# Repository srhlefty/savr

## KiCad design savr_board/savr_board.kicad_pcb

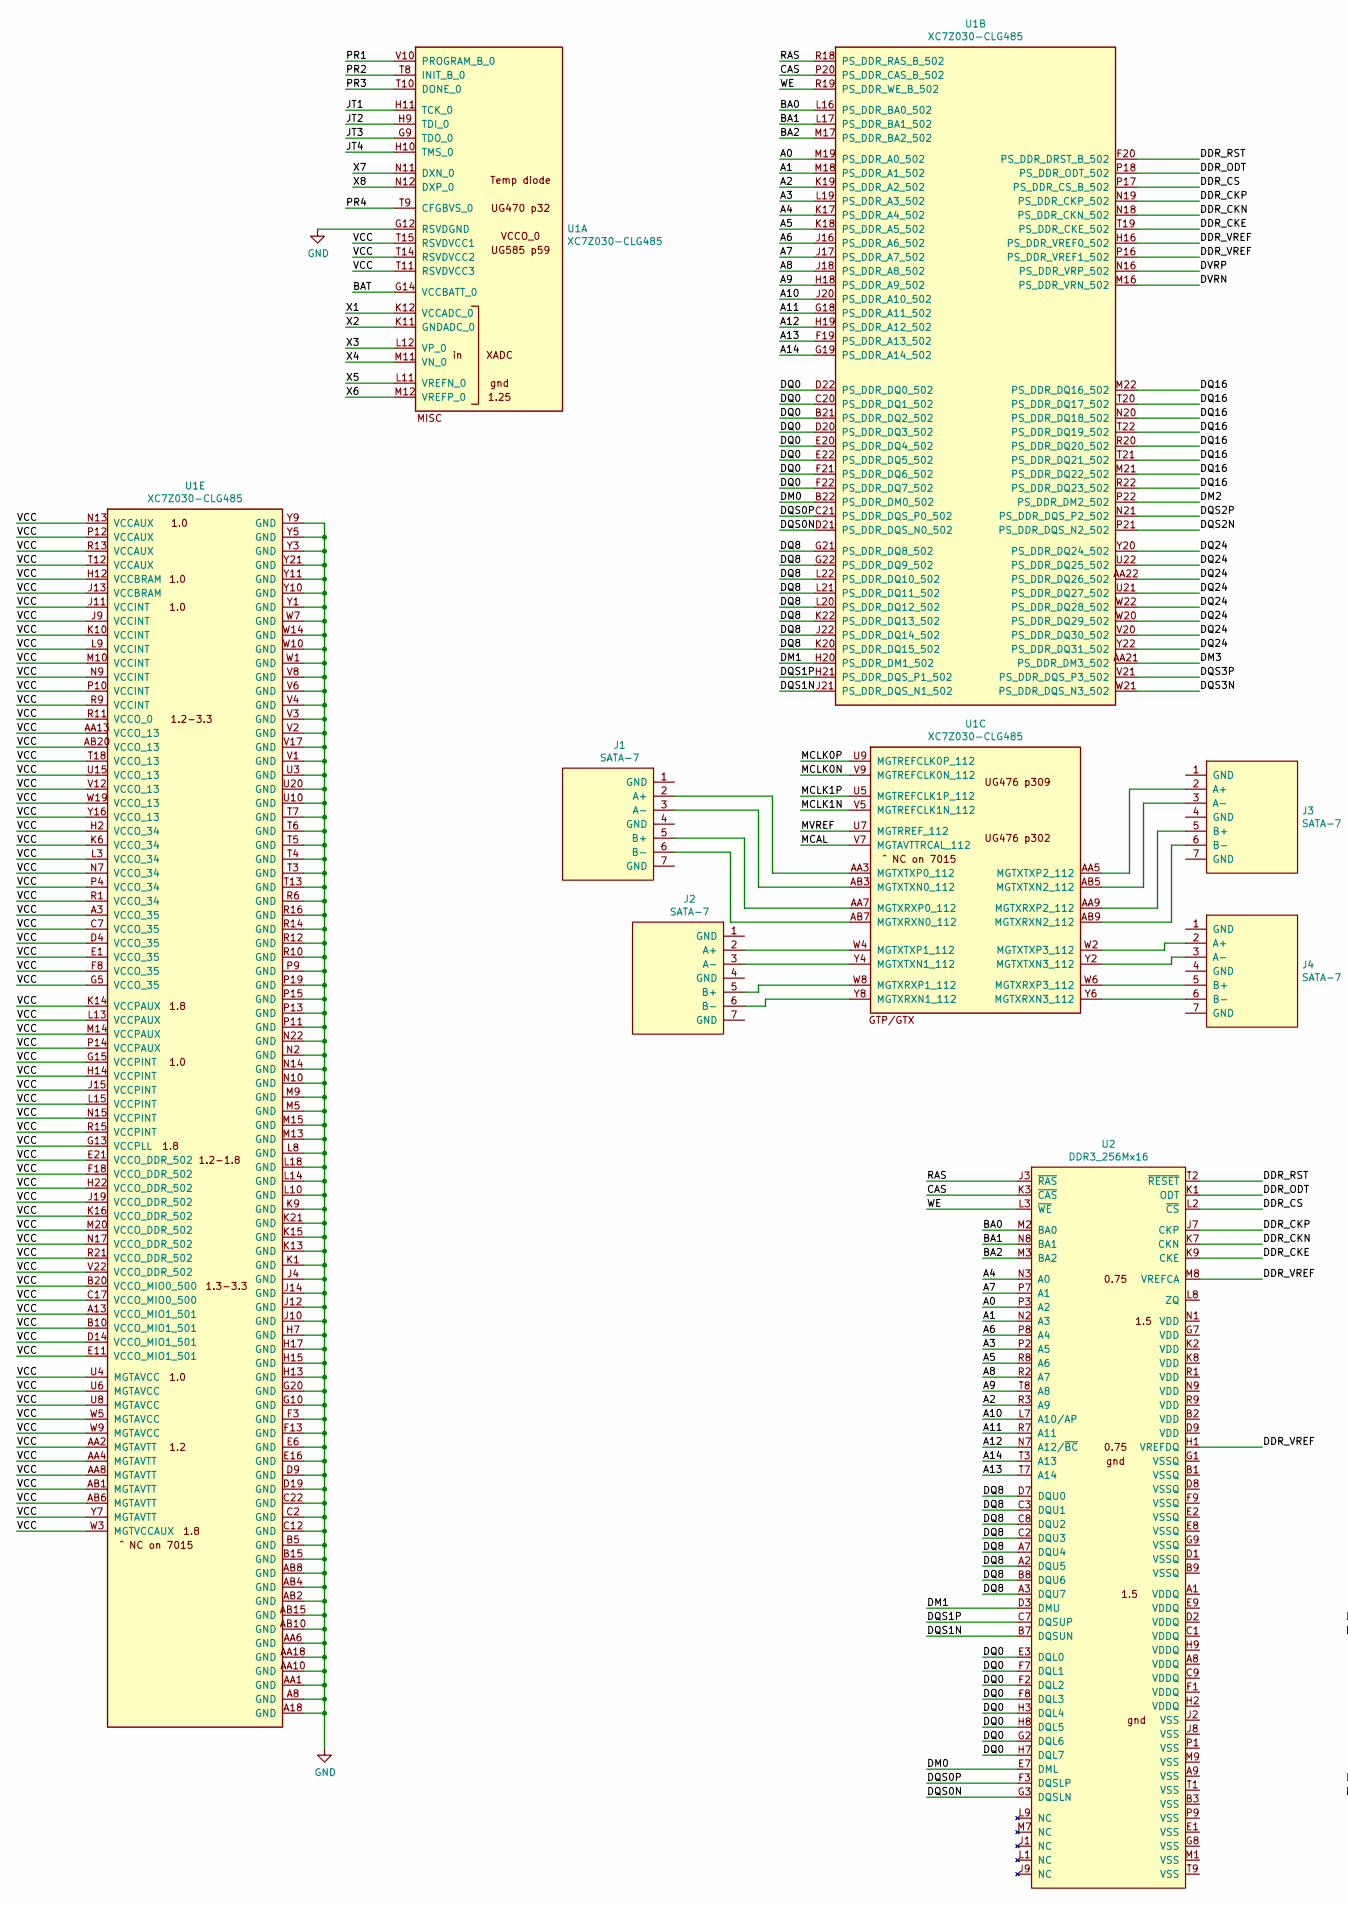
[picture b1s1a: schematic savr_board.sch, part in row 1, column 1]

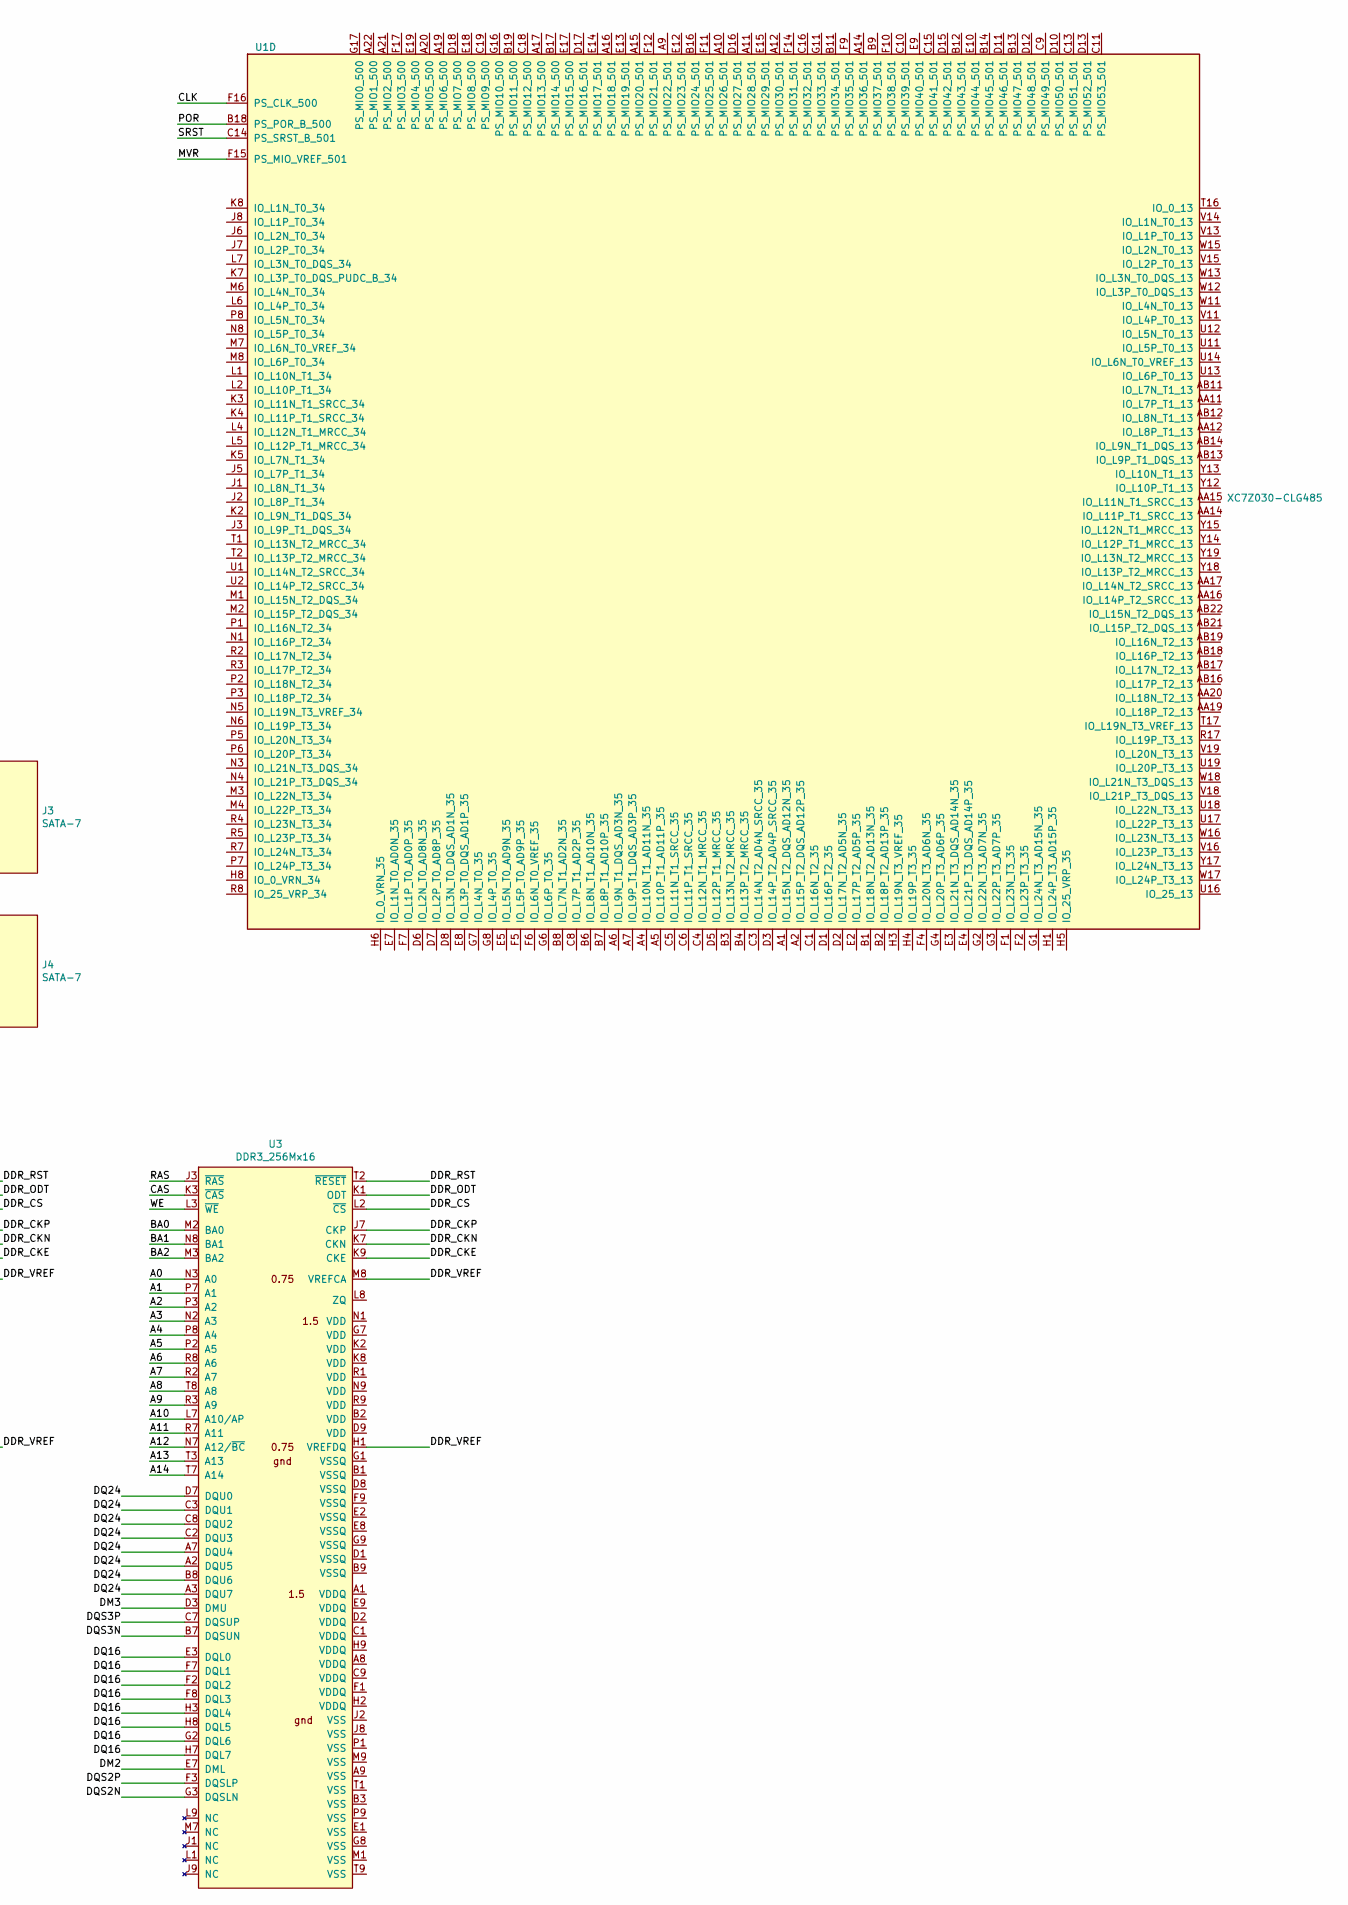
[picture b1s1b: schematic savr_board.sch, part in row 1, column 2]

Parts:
J1, J2, J3, J4: SATA-7
U1: XC7Z030-CLG485; BGA-484_22x22_19.0x19.0mm
U2, U3: DDR3_256Mx16; BGA-96_9x16_9.0x13.5mm

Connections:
/A0: U1.M19 (PS_DDR_A0_502), U2.P3 (A2), U3.N3 (A0)
/A1: U1.M18 (PS_DDR_A1_502), U2.N2 (A3), U3.P7 (A1)
/A2: U1.K19 (PS_DDR_A2_502), U2.R3 (A9), U3.P3 (A2)
/A3: U1.L19 (PS_DDR_A3_502), U2.P2 (A5), U3.N2 (A3)
/A4: U1.K17 (PS_DDR_A4_502), U2.N3 (A0), U3.P8 (A4)
/A5: U1.K18 (PS_DDR_A5_502), U2.R8 (A6), U3.P2 (A5)
/A6: U1.J16 (PS_DDR_A6_502), U2.P8 (A4), U3.R8 (A6)
/A7: U1.J17 (PS_DDR_A7_502), U2.P7 (A1), U3.R2 (A7)
/A8: U1.J18 (PS_DDR_A8_502), U2.R2 (A7), U3.T8 (A8)
/A9: U1.H18 (PS_DDR_A9_502), U2.T8 (A8), U3.R3 (A9)
/A10: U1.J20 (PS_DDR_A10_502), U2.L7 (A10/AP), U3.L7 (A10/AP)
/A11: U1.G18 (PS_DDR_A11_502), U2.R7 (A11), U3.R7 (A11)
/A12: U1.H19 (PS_DDR_A12_502), U2.N7 (A12/~BC~), U3.N7 (A12/~BC~)
/A13: U1.F19 (PS_DDR_A13_502), U2.T7 (A14), U3.T3 (A13)
/A14: U1.G19 (PS_DDR_A14_502), U2.T3 (A13), U3.T7 (A14)
/BA0: U1.L16 (PS_DDR_BA0_502), U2.M2 (BA0), U3.M2 (BA0)
/BA1: U1.L17 (PS_DDR_BA1_502), U2.N8 (BA1), U3.N8 (BA1)
/BA2: U1.M17 (PS_DDR_BA2_502), U2.M3 (BA2), U3.M3 (BA2)
/BAT: U1.G14 (VCCBATT_0)
/CAS: U1.P20 (PS_DDR_CAS_B_502), U2.K3 (~CAS~), U3.K3 (~CAS~)
/CLK: U1.F16 (PS_CLK_500)
/DDR_CKE: U1.T19 (PS_DDR_CKE_502), U2.K9 (CKE), U3.K9 (CKE)
/DDR_CKN: U1.N18 (PS_DDR_CKN_502), U2.K7 (CKN), U3.K7 (CKN)
/DDR_CKP: U1.N19 (PS_DDR_CKP_502), U2.J7 (CKP), U3.J7 (CKP)
/DDR_CS: U1.P17 (PS_DDR_CS_B_502), U2.L2 (~CS~), U3.L2 (~CS~)
/DDR_ODT: U1.P18 (PS_DDR_ODT_502), U2.K1 (ODT), U3.K1 (ODT)
/DDR_RST: U1.F20 (PS_DDR_DRST_B_502), U2.T2 (~RESET~), U3.T2 (~RESET~)
/DDR_VREF: U1.H16 (PS_DDR_VREF0_502), U1.P16 (PS_DDR_VREF1_502), U2.H1 (VREFDQ), U2.M8 (VREFCA), U3.H1 (VREFDQ), U3.M8 (VREFCA)
/DM0: U1.B22 (PS_DDR_DM0_502), U2.E7 (DML)
/DM1: U1.H20 (PS_DDR_DM1_502), U2.D3 (DMU)
/DM2: U1.P22 (PS_DDR_DM2_502), U3.E7 (DML)
/DM3: U1.AA21 (PS_DDR_DM3_502), U3.D3 (DMU)
/DQ0: U1.B21 (PS_DDR_DQ2_502), U1.C20 (PS_DDR_DQ1_502), U1.D20 (PS_DDR_DQ3_502), U1.D22 (PS_DDR_DQ0_502), U1.E20 (PS_DDR_DQ4_502), U1.E22 (PS_DDR_DQ5_502), U1.F21 (PS_DDR_DQ6_502), U1.F22 (PS_DDR_DQ7_502), U2.E3 (DQL0), U2.F2 (DQL2), U2.F7 (DQL1), U2.F8 (DQL3), U2.G2 (DQL6), U2.H3 (DQL4), U2.H7 (DQL7), U2.H8 (DQL5)
/DQ8: U1.G21 (PS_DDR_DQ8_502), U1.G22 (PS_DDR_DQ9_502), U1.J22 (PS_DDR_DQ14_502), U1.K20 (PS_DDR_DQ15_502), U1.K22 (PS_DDR_DQ13_502), U1.L20 (PS_DDR_DQ12_502), U1.L21 (PS_DDR_DQ11_502), U1.L22 (PS_DDR_DQ10_502), U2.A2 (DQU5), U2.A3 (DQU7), U2.A7 (DQU4), U2.B8 (DQU6), U2.C2 (DQU3), U2.C3 (DQU1), U2.C8 (DQU2), U2.D7 (DQU0)
/DQ16: U1.M21 (PS_DDR_DQ22_502), U1.M22 (PS_DDR_DQ16_502), U1.N20 (PS_DDR_DQ18_502), U1.R20 (PS_DDR_DQ20_502), U1.R22 (PS_DDR_DQ23_502), U1.T20 (PS_DDR_DQ17_502), U1.T21 (PS_DDR_DQ21_502), U1.T22 (PS_DDR_DQ19_502), U3.E3 (DQL0), U3.F2 (DQL2), U3.F7 (DQL1), U3.F8 (DQL3), U3.G2 (DQL6), U3.H3 (DQL4), U3.H7 (DQL7), U3.H8 (DQL5)
/DQ24: U1.AA22 (PS_DDR_DQ26_502), U1.U21 (PS_DDR_DQ27_502), U1.U22 (PS_DDR_DQ25_502), U1.V20 (PS_DDR_DQ30_502), U1.W20 (PS_DDR_DQ29_502), U1.W22 (PS_DDR_DQ28_502), U1.Y20 (PS_DDR_DQ24_502), U1.Y22 (PS_DDR_DQ31_502), U3.A2 (DQU5), U3.A3 (DQU7), U3.A7 (DQU4), U3.B8 (DQU6), U3.C2 (DQU3), U3.C3 (DQU1), U3.C8 (DQU2), U3.D7 (DQU0)
/DQS0N: U1.D21 (PS_DDR_DQS_N0_502), U2.G3 (DQSLN)
/DQS0P: U1.C21 (PS_DDR_DQS_P0_502), U2.F3 (DQSLP)
/DQS1N: U1.J21 (PS_DDR_DQS_N1_502), U2.B7 (DQSUN)
/DQS1P: U1.H21 (PS_DDR_DQS_P1_502), U2.C7 (DQSUP)
/DQS2N: U1.P21 (PS_DDR_DQS_N2_502), U3.G3 (DQSLN)
/DQS2P: U1.N21 (PS_DDR_DQS_P2_502), U3.F3 (DQSLP)
/DQS3N: U1.W21 (PS_DDR_DQS_N3_502), U3.B7 (DQSUN)
/DQS3P: U1.V21 (PS_DDR_DQS_P3_502), U3.C7 (DQSUP)
/DVRN: U1.M16 (PS_DDR_VRN_502)
/DVRP: U1.N16 (PS_DDR_VRP_502)
/JT1: U1.H11 (TCK_0)
/JT2: U1.H9 (TDI_0)
/JT3: U1.G9 (TDO_0)
/JT4: U1.H10 (TMS_0)
/MCAL: U1.V7 (MGTAVTTRCAL_112)
/MCLK0N: U1.V9 (MGTREFCLK0N_112)
/MCLK0P: U1.U9 (MGTREFCLK0P_112)
/MCLK1N: U1.V5 (MGTREFCLK1N_112)
/MCLK1P: U1.U5 (MGTREFCLK1P_112)
/MVR: U1.F15 (PS_MIO_VREF_501)
/MVREF: U1.U7 (MGTRREF_112)
/POR: U1.B18 (PS_POR_B_500)
/PR1: U1.V10 (PROGRAM_B_0)
/PR2: U1.T8 (INIT_B_0)
/PR3: U1.T10 (DONE_0)
/PR4: U1.T9 (CFGBVS_0)
/RAS: U1.R18 (PS_DDR_RAS_B_502), U2.J3 (~RAS~), U3.J3 (~RAS~)
/SRST: U1.C14 (PS_SRST_B_501)
/VCC: U1.A3 (VCCO_35), U1.A13 (VCCO_MIO1_501), U1.AA2 (MGTAVTT), U1.AA4 (MGTAVTT), U1.AA8 (MGTAVTT), U1.AA13 (VCCO_13), U1.AB1 (MGTAVTT), U1.AB6 (MGTAVTT), U1.AB20 (VCCO_13), U1.B10 (VCCO_MIO1_501), U1.B20 (VCCO_MIO0_500), U1.C7 (VCCO_35), U1.C17 (VCCO_MIO0_500), U1.D4 (VCCO_35), U1.D14 (VCCO_MIO1_501), U1.E1 (VCCO_35), U1.E11 (VCCO_MIO1_501), U1.E21 (VCCO_DDR_502), U1.F8 (VCCO_35), U1.F18 (VCCO_DDR_502), U1.G5 (VCCO_35), U1.G13 (VCCPLL), U1.G15 (VCCPINT), U1.H2 (VCCO_34), U1.H12 (VCCBRAM), U1.H14 (VCCPINT), U1.H22 (VCCO_DDR_502), U1.J9 (VCCINT), U1.J11 (VCCINT), U1.J13 (VCCBRAM), U1.J15 (VCCPINT), U1.J19 (VCCO_DDR_502), U1.K6 (VCCO_34), U1.K10 (VCCINT), U1.K14 (VCCPAUX), U1.K16 (VCCO_DDR_502), U1.L3 (VCCO_34), U1.L9 (VCCINT), U1.L13 (VCCPAUX), U1.L15 (VCCPINT), U1.M10 (VCCINT), U1.M14 (VCCPAUX), U1.M20 (VCCO_DDR_502), U1.N7 (VCCO_34), U1.N9 (VCCINT), U1.N13 (VCCAUX), U1.N15 (VCCPINT), U1.N17 (VCCO_DDR_502), U1.P4 (VCCO_34), U1.P10 (VCCINT), U1.P12 (VCCAUX), U1.P14 (VCCPAUX), U1.R1 (VCCO_34), U1.R9 (VCCINT), U1.R11 (VCCO_0), U1.R13 (VCCAUX), U1.R15 (VCCPINT), U1.R21 (VCCO_DDR_502), U1.T11 (RSVDVCC3), U1.T12 (VCCAUX), U1.T14 (RSVDVCC2), U1.T15 (RSVDVCC1), U1.T18 (VCCO_13), U1.U4 (MGTAVCC), U1.U6 (MGTAVCC), U1.U8 (MGTAVCC), U1.U15 (VCCO_13), U1.V12 (VCCO_13), U1.V22 (VCCO_DDR_502), U1.W3 (MGTVCCAUX), U1.W5 (MGTAVCC), U1.W9 (MGTAVCC), U1.W19 (VCCO_13), U1.Y7 (MGTAVTT), U1.Y16 (VCCO_13)
/WE: U1.R19 (PS_DDR_WE_B_502), U2.L3 (~WE~), U3.L3 (~WE~)
/X1: U1.K12 (VCCADC_0)
/X2: U1.K11 (GNDADC_0)
/X3: U1.L12 (VP_0)
/X4: U1.M11 (VN_0)
/X5: U1.L11 (VREFN_0)
/X6: U1.M12 (VREFP_0)
/X7: U1.N11 (DXN_0)
/X8: U1.N12 (DXP_0)
GND: U1.A8 (GND), U1.A18 (GND), U1.AA1 (GND), U1.AA6 (GND), U1.AA10 (GND), U1.AA18 (GND), U1.AB2 (GND), U1.AB4 (GND), U1.AB8 (GND), U1.AB10 (GND), U1.AB15 (GND), U1.B5 (GND), U1.B15 (GND), U1.C2 (GND), U1.C12 (GND), U1.C22 (GND), U1.D9 (GND), U1.D19 (GND), U1.E6 (GND), U1.E16 (GND), U1.F3 (GND), U1.F13 (GND), U1.G10 (GND), U1.G12 (RSVDGND), U1.G20 (GND), U1.H7 (GND), U1.H13 (GND), U1.H15 (GND), U1.H17 (GND), U1.J4 (GND), U1.J10 (GND), U1.J12 (GND), U1.J14 (GND), U1.K1 (GND), U1.K9 (GND), U1.K13 (GND), U1.K15 (GND), U1.K21 (GND), U1.L8 (GND), U1.L10 (GND), U1.L14 (GND), U1.L18 (GND), U1.M5 (GND), U1.M9 (GND), U1.M13 (GND), U1.M15 (GND), U1.N2 (GND), U1.N10 (GND), U1.N14 (GND), U1.N22 (GND), U1.P9 (GND), U1.P11 (GND), U1.P13 (GND), U1.P15 (GND), U1.P19 (GND), U1.R6 (GND), U1.R10 (GND), U1.R12 (GND), U1.R14 (GND), U1.R16 (GND), U1.T3 (GND), U1.T4 (GND), U1.T5 (GND), U1.T6 (GND), U1.T7 (GND), U1.T13 (GND), U1.U3 (GND), U1.U10 (GND), U1.U20 (GND), U1.V1 (GND), U1.V2 (GND), U1.V3 (GND), U1.V4 (GND), U1.V6 (GND), U1.V8 (GND), U1.V17 (GND), U1.W1 (GND), U1.W7 (GND), U1.W10 (GND), U1.W14 (GND), U1.Y1 (GND), U1.Y3 (GND), U1.Y5 (GND), U1.Y9 (GND), U1.Y10 (GND), U1.Y11 (GND), U1.Y21 (GND)
unnamed: J1.2 (A+), U1.AA3 (MGTXTXP0_112)
unnamed: J1.3 (A-), U1.AB3 (MGTXTXN0_112)
unnamed: J1.5 (B+), U1.AA7 (MGTXRXP0_112)
unnamed: J1.6 (B-), U1.AB7 (MGTXRXN0_112)
unnamed: J2.2 (A+), U1.W4 (MGTXTXP1_112)
unnamed: J2.3 (A-), U1.Y4 (MGTXTXN1_112)
unnamed: J2.5 (B+), U1.W8 (MGTXRXP1_112)
unnamed: J2.6 (B-), U1.Y8 (MGTXRXN1_112)
unnamed: J3.2 (A+), U1.AA5 (MGTXTXP2_112)
unnamed: J3.3 (A-), U1.AB5 (MGTXTXN2_112)
unnamed: J3.5 (B+), U1.AA9 (MGTXRXP2_112)
unnamed: J3.6 (B-), U1.AB9 (MGTXRXN2_112)
unnamed: J4.2 (A+), U1.W2 (MGTXTXP3_112)
unnamed: J4.3 (A-), U1.Y2 (MGTXTXN3_112)
unnamed: J4.5 (B+), U1.W6 (MGTXRXP3_112)
unnamed: J4.6 (B-), U1.Y6 (MGTXRXN3_112)

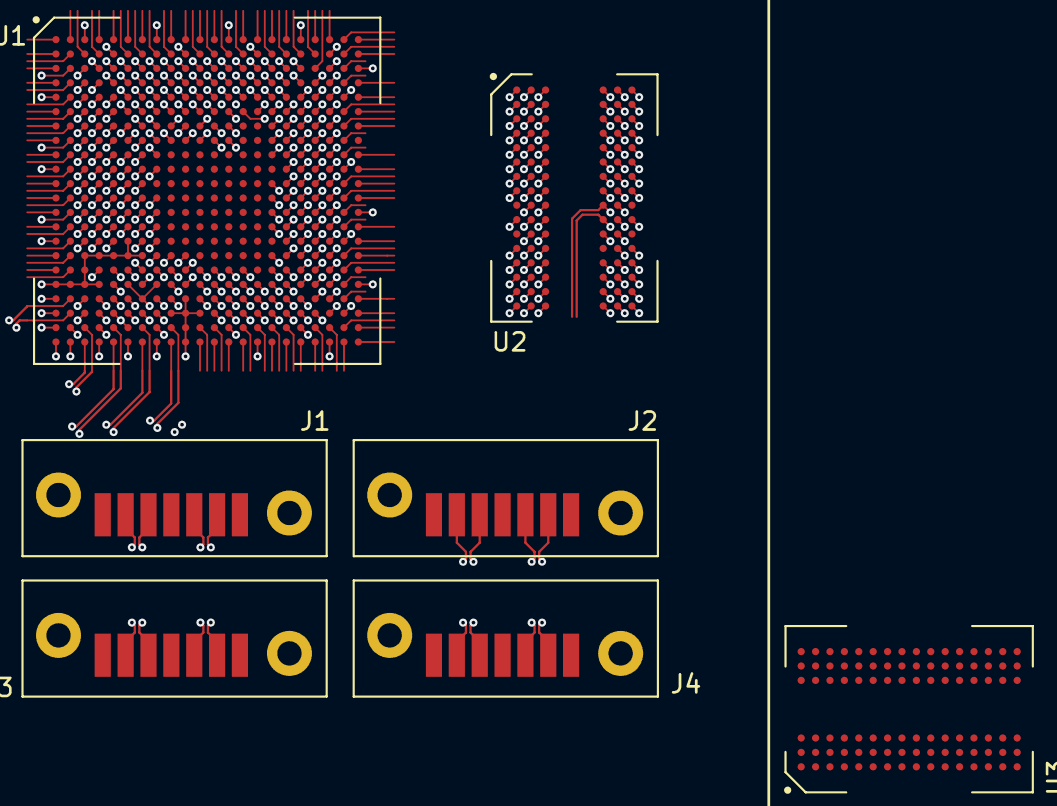
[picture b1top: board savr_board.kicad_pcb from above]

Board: 6 copper layers, 7 parts (0 on the bottom side), 62 nets.

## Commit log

2019-04-03 Parts for initial concept. Zynq 015 because it has GTP transceivers which go up to 3Gbps, suitable for SATA II. That package is also pin compatible with a Zynq 030, which has GTX transceivers that ca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
2019-04-03 More part selection
2019-04-05 Added SATA alt and power rail requirements
2019-04-07 Downloaded pinout tables for the Zynq parts I'm targeting. As expected they are largely pin-compatible: the only exception is a pair of pins associated with the GTX transceivers in the 030. One extra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
2019-04-07 Created a symbol for the Zynq part, added the guides I've needed so far to determine pin functions
2019-04-09 Made ddr3 symbol
2019-04-10 Set pin directions on ddr symbol
2019-04-10 Not really sure what happened
2019-04-10 Added symbol for usb-uart
2019-04-10 Added ethernet phy symbol
2019-04-11 Added footprints for fpga, ddr, and sata. Did the minimum amount of wiring to see whether it's feasible to put those on a 50x50mm JLCPCB cheapo board. Looks pretty bleak with thru-hole SATA connector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
2019-04-12 Forgot these I think
2019-04-12 Escape routing for the first 5 rows, not paying special attention to differentials
2019-04-12 I did it! Complete escape with 4 signal layers. There are a few places where I might have to rip something up: the VRP / VRN nets require resistors to ground and vcc, so those must have bottom layer 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
2019-04-13 Feasibility test of IO connectors and SATA routing
2019-04-17 Did a bunch of escape reshuffling and managed to route the DDR address and control lines. This probably won't work though since A10 and A12 have dual functionality that the CPU might use.
2019-04-17 Pin swaps to support A10/A12 being the same. I don't like this much since I had to put them on a different layer.
2019-04-19 More routing tests for DDR
2019-04-19 Initial sketch of Altium workspace
2019-04-19 Configured stackup for jlcpcb 6-layer
2019-04-19 First stab at jlcpcb design rules Min trace/space for 6-layer is 3.5, but I set it to 5 here to be conservative. Same with min via size, I put preferred size slightly larger than the minimum. Differe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
2019-04-19 Update board shape to 100x50mm
2019-04-19 Nevermind, 100x100 is the same price
2019-04-19 Created footprints for zynq, ddr, ethernet phy, and sata
2019-04-21 Made symbol for Zynq
2019-04-21 Added symbols for DDR3 and ethernet phy and sata
2019-04-21 Materials for ethernet jack
2019-04-21 Made ethernet connector symbol
2019-04-21 Copied over some symbols from lanemate, added 3d bodies for hdmi, power jack, and sata connector
2019-04-24 Copied fpga power excluding banks from microzed
2019-04-24 Microsd slot datasheet and cad model
2019-04-25 Added Mini-ITX ref design. Shows how to wire up the SATA connector and reference clock.
2019-04-26 Added Mini ITX hardware guide since it talks about the SATA reference clock
